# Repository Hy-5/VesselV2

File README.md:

# VesselV2
 Keyboard PCB build#2

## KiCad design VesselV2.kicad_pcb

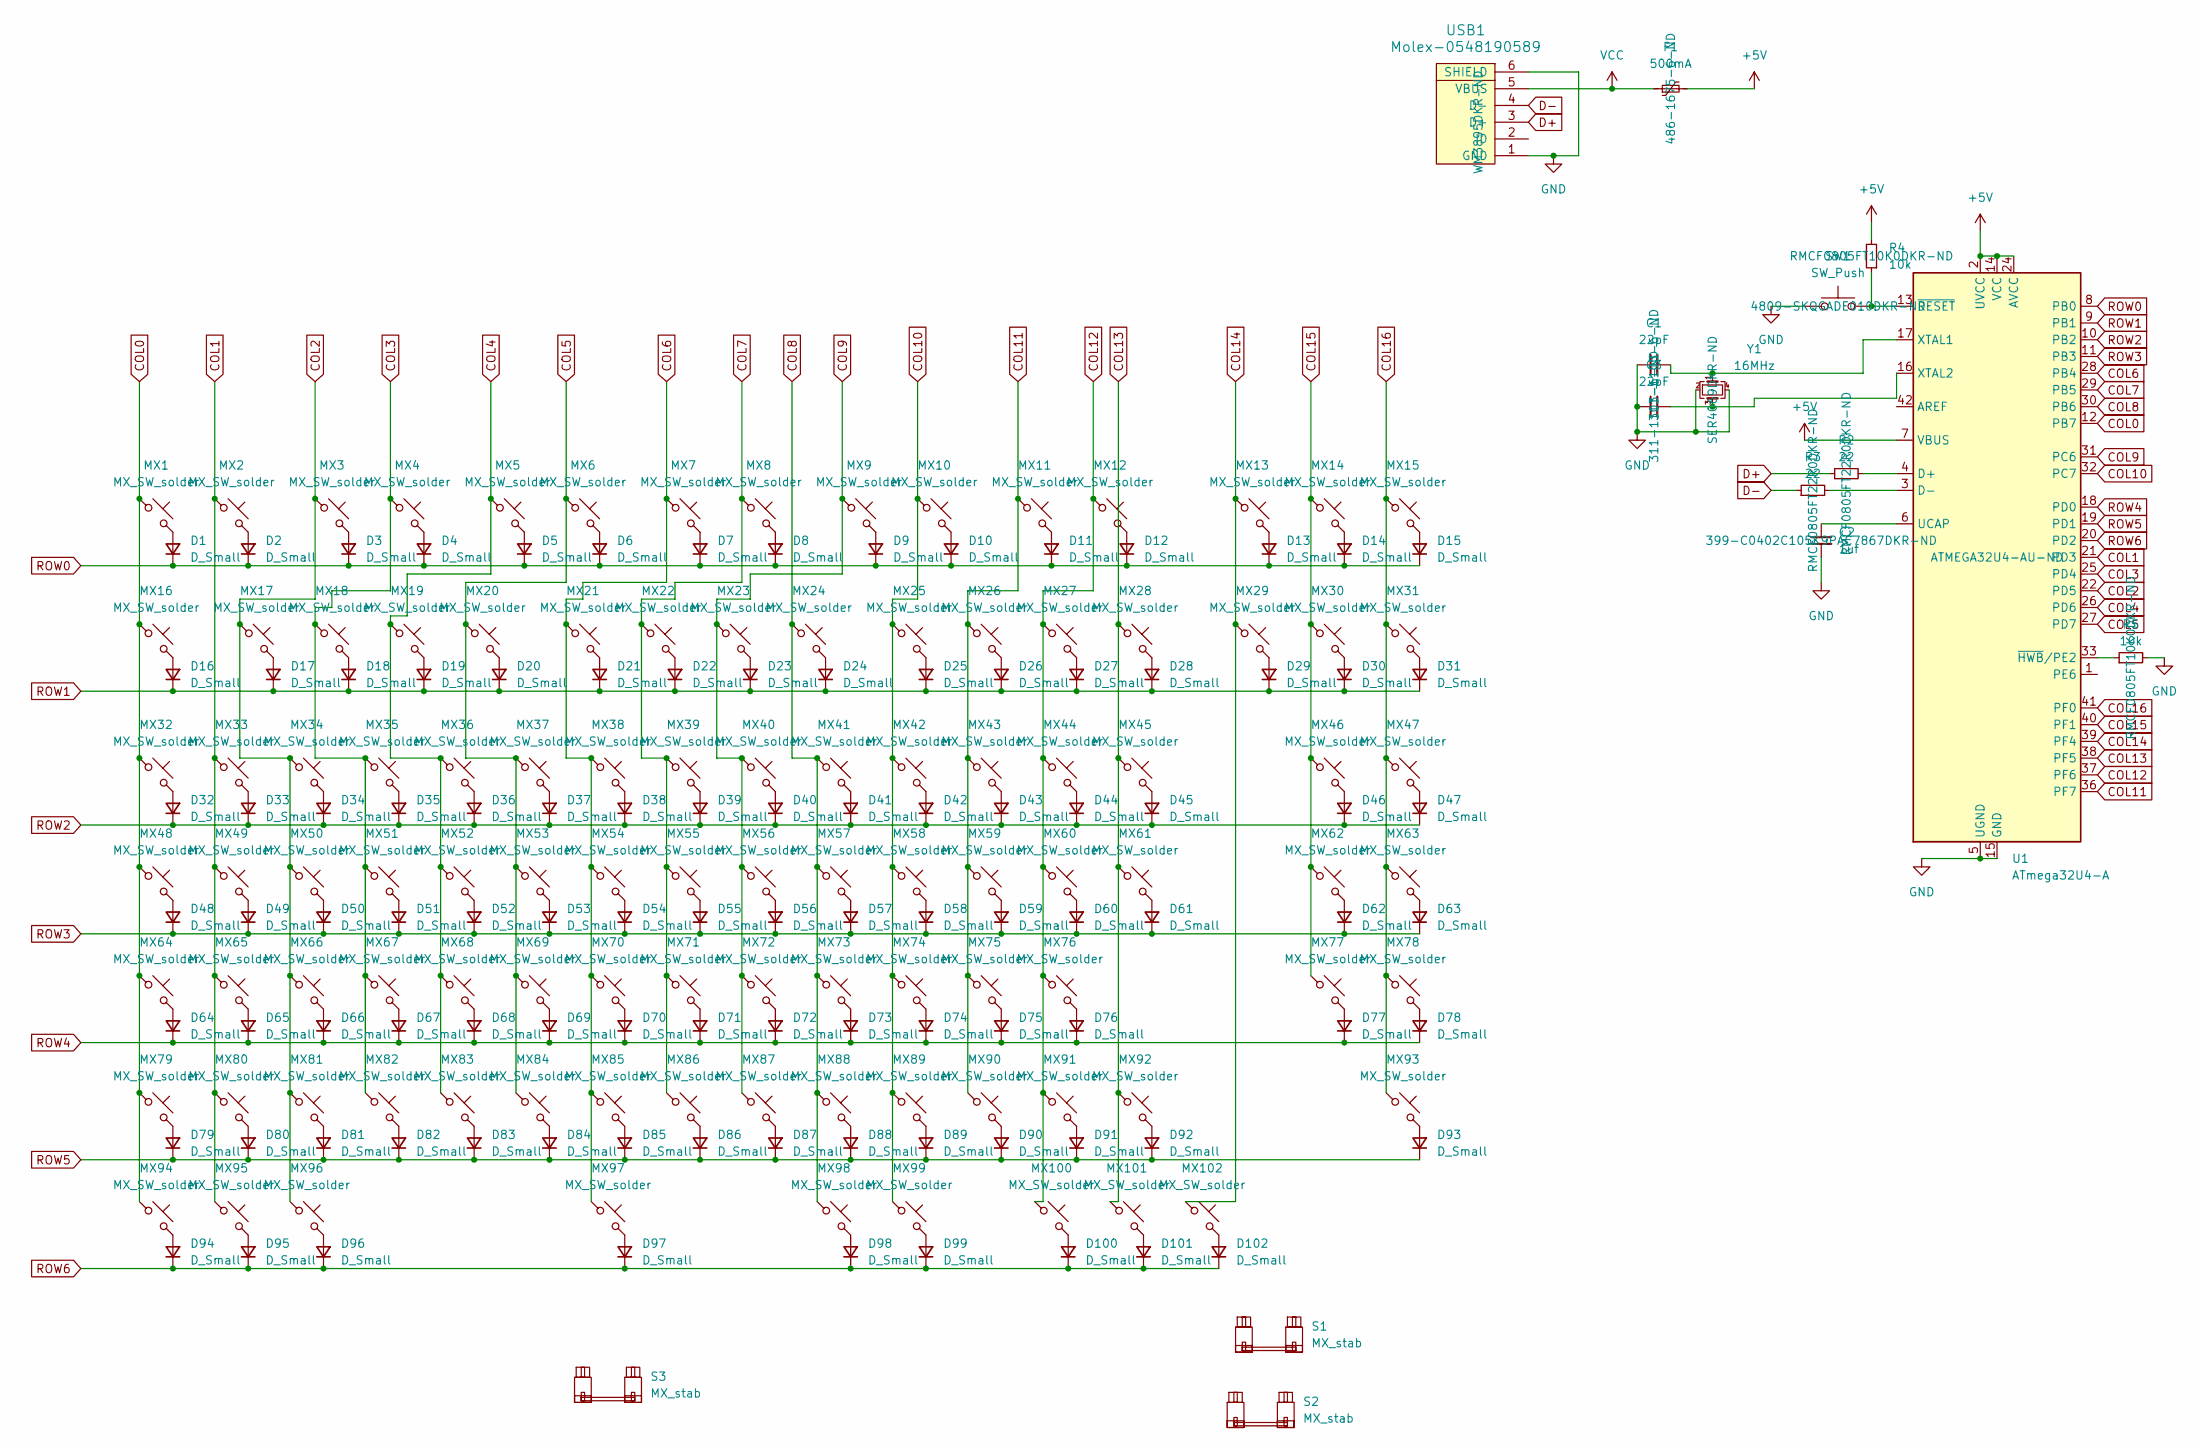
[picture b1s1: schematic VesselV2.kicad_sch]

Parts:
C1, C3: 22pF; C_0805_2012Metric_Pad1.18x1.45mm_HandSolder; MouserPartNumber 603-CC805JRNPO9BN220; DigikeyPartNumber 311-1103-6-ND
C2: 1uf; C_0805_2012Metric_Pad1.18x1.45mm_HandSolder; MouserPartNumber 80-C0402C105K9P; DigikeyPartNumber 399-C0402C105K9PAC7867DKR-ND
D1, D2, D3, D4, D5, D6, D7, D8, D9, D10, D11, D12, D13, D14, D15, D16, D17, D18, D19, D20, D21, D22, D23, D24, D25, D26, D27, D28, D29, D30, D31, D32, D33, D34, D35, D36, D37, D38, D39, D40, D41, D42, D43, D44, D45, D46, D47, D48, D49, D50, D51, D52, D53, D54, D55, D56, D57, D58, D59, D60, D61, D62, D63, D64, D65, D66, D67, D68, D69, D70, D71, D72, D73, D74, D75, D76, D77, D78, D79, D80, D81, D82, D83, D84, D85, D86, D87, D88, D89, D90, D91, D92, D93, D94, D95, D96, D97, D98, D99, D100, D101, D102: D_Small; D_SOD-123; ManufacturerPartNumber 1N4148W; DigikeyPartNumber 1N4148WTPMSDKR-ND
F1: 500mA; Fuse_1206_3216Metric_Pad1.42x1.75mm_HandSolder; MouserPartNumber 693-3413.0113.22; DigikeyPartNumber 486-1675-6-ND
MX1, MX2, MX3, MX4, MX5, MX6, MX7, MX8, MX9, MX10, MX11, MX12, MX13, MX14, MX15, MX16, MX17, MX18, MX19, MX20, MX21, MX22, MX23, MX24, MX25, MX26, MX27, MX28, MX29, MX30, MX31, MX32, MX33, MX34, MX35, MX36, MX37, MX38, MX39, MX40, MX41, MX42, MX43, MX44, MX46, MX47, MX49, MX50, MX51, MX52, MX53, MX54, MX55, MX56, MX57, MX58, MX59, MX60, MX62, MX63, MX65, MX66, MX67, MX68, MX69, MX70, MX71, MX72, MX73, MX74, MX75, MX76, MX77, MX78, MX80, MX81, MX82, MX83, MX84, MX85, MX86, MX87, MX88, MX89, MX90, MX92, MX93, MX100, MX101, MX102: MX_SW_solder; SW_Cherry_MX_PCB_1.00u
MX45: MX_SW_solder; SW_Cherry_MX_PCB_2.00u
MX48: MX_SW_solder; SW_Cherry_MX_PCB_1.50u
MX61: MX_SW_solder; SW_Cherry_MX_PCB_ISOEnter
MX64, MX91: MX_SW_solder; SW_Cherry_MX_PCB_1.75u
MX79, MX94, MX95, MX96, MX98, MX99: MX_SW_solder; SW_Cherry_MX_PCB_1.25u
MX97: MX_SW_solder; SW_Cherry_MX_PCB_6.25u
R2, R3: 22; R_0805_2012Metric_Pad1.20x1.40mm_HandSolder; MouserPartNumber 708-RMCF0805FT22R0; DigikeyPartNumber RMCF0805FT22R0DKR-ND
R4, R5: 10k; R_0805_2012Metric_Pad1.20x1.40mm_HandSolder; MouserPartNumber 708-RMCF0805FT10K0; DigikeyPartNumber RMCF0805FT10K0DKR-ND
S1, S2: MX_stab; Stabilizer_Cherry_MX_2.00u
S3: MX_stab; Stabilizer_Cherry_MX_6.25u
SW1: SW_Push; SKQG-1155865; ManufacturerPartNumber SKQGACE010; DigikeyPartNumber 4809-SKQGADE010DKR-ND
U1: ATmega32U4-A; TQFP-44_10x10mm_P0.8mm; MouserPartNumber 556-ATMEGA32U4-AU; DigikeyPartNumber ATMEGA32U4-AU-ND
USB1: Molex-0548190589; ManufacturerPartNumber 548190589; DigikeyPartNumber WM3895DKR-ND
Y1: 16MHz; Crystal_SMD_3225-4Pin_3.2x2.5mm_HandSoldering; MouserPartNumber 732-322516MF09Z-AC0; DigikeyPartNumber SER4069DKR-ND

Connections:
+5V: F1.2, R4.2, U1.2 (UVCC), U1.7 (VBUS), U1.14 (VCC), U1.24 (AVCC), U1.34 (VCC), U1.44 (AVCC)
COL0: MX1.1, MX16.1, MX32.1, MX48.1, MX64.1, MX79.1, MX94.1, U1.12 (PB7)
COL1: MX2.1, MX33.1, MX49.1, MX65.1, MX80.1, MX95.1, U1.21 (PD3)
COL2: MX3.1, MX17.1, MX34.1, MX50.1, MX66.1, MX81.1, MX96.1, U1.22 (PD5)
COL3: MX4.1, MX18.1, MX35.1, MX51.1, MX67.1, MX82.1, U1.25 (PD4)
COL4: MX5.1, MX19.1, MX36.1, MX52.1, MX68.1, MX83.1, U1.26 (PD6)
COL5: MX6.1, MX20.1, MX37.1, MX53.1, MX69.1, MX84.1, U1.27 (PD7)
COL6: MX7.1, MX21.1, MX38.1, MX54.1, MX70.1, MX85.1, MX97.1, U1.28 (PB4)
COL7: MX8.1, MX22.1, MX39.1, MX55.1, MX71.1, MX86.1, U1.29 (PB5)
COL8: MX24.1, MX41.1, MX57.1, MX73.1, MX88.1, MX98.1, U1.30 (PB6)
COL9: MX9.1, MX23.1, MX40.1, MX56.1, MX72.1, MX87.1, U1.31 (PC6)
COL10: MX10.1, MX25.1, MX42.1, MX58.1, MX74.1, MX89.1, MX99.1, U1.32 (PC7)
COL11: MX11.1, MX26.1, MX43.1, MX59.1, MX75.1, MX90.1, U1.36 (PF7)
COL12: MX12.1, MX27.1, MX44.1, MX60.1, MX76.1, MX91.1, MX100.1, U1.37 (PF6)
COL13: MX28.1, MX45.1, MX61.1, MX92.1, MX101.1, U1.38 (PF5)
COL14: MX13.1, MX29.1, MX102.1, U1.39 (PF4)
COL15: MX14.1, MX30.1, MX46.1, MX62.1, MX77.1, U1.40 (PF1)
COL16: MX15.1, MX31.1, MX47.1, MX63.1, MX78.1, MX93.1, U1.41 (PF0)
D+: R2.1, USB1.3 (D+)
D-: R3.1, USB1.4 (D-)
GND: C1.1, C2.2, C3.1, R5.2, SW1.1, U1.5 (UGND), U1.15 (GND), U1.23 (GND), U1.35 (GND), U1.43 (GND), USB1.1 (GND), USB1.6 (SHIELD), Y1.2, Y1.4
unnamed: D1.2 (A), MX1.2
unnamed: D2.2 (A), MX2.2
unnamed: D3.2 (A), MX3.2
unnamed: D4.2 (A), MX4.2
unnamed: D5.2 (A), MX5.2
unnamed: D6.2 (A), MX6.2
unnamed: D7.2 (A), MX7.2
unnamed: D8.2 (A), MX8.2
unnamed: D9.2 (A), MX9.2
unnamed: D10.2 (A), MX10.2
unnamed: D11.2 (A), MX11.2
unnamed: D12.2 (A), MX12.2
unnamed: D13.2 (A), MX13.2
unnamed: D14.2 (A), MX14.2
unnamed: D15.2 (A), MX15.2
unnamed: D16.2 (A), MX16.2
unnamed: D17.2 (A), MX17.2
unnamed: D18.2 (A), MX18.2
unnamed: D19.2 (A), MX19.2
unnamed: D20.2 (A), MX20.2
unnamed: D21.2 (A), MX21.2
unnamed: D22.2 (A), MX22.2
unnamed: D23.2 (A), MX23.2
unnamed: D24.2 (A), MX24.2
unnamed: D25.2 (A), MX25.2
unnamed: D26.2 (A), MX26.2
unnamed: D27.2 (A), MX27.2
unnamed: D28.2 (A), MX28.2
unnamed: D29.2 (A), MX29.2
unnamed: D30.2 (A), MX30.2
unnamed: D31.2 (A), MX31.2
unnamed: D32.2 (A), MX32.2
unnamed: D33.2 (A), MX33.2
unnamed: D34.2 (A), MX34.2
unnamed: D35.2 (A), MX35.2
unnamed: D36.2 (A), MX36.2
unnamed: D37.2 (A), MX37.2
unnamed: D38.2 (A), MX38.2
unnamed: D39.2 (A), MX39.2
unnamed: D40.2 (A), MX40.2
unnamed: D41.2 (A), MX41.2
unnamed: D42.2 (A), MX42.2
unnamed: D43.2 (A), MX43.2
unnamed: D44.2 (A), MX44.2
unnamed: D45.2 (A), MX45.2
unnamed: D46.2 (A), MX46.2
unnamed: D47.2 (A), MX47.2
unnamed: D48.2 (A), MX48.2
unnamed: D49.2 (A), MX49.2
unnamed: D50.2 (A), MX50.2
unnamed: D51.2 (A), MX51.2
unnamed: D52.2 (A), MX52.2
unnamed: D53.2 (A), MX53.2
unnamed: D54.2 (A), MX54.2
unnamed: D55.2 (A), MX55.2
unnamed: D56.2 (A), MX56.2
unnamed: D57.2 (A), MX57.2
unnamed: D58.2 (A), MX58.2
unnamed: D59.2 (A), MX59.2
unnamed: D60.2 (A), MX60.2
unnamed: D61.2 (A), MX61.2
unnamed: D62.2 (A), MX62.2
unnamed: D63.2 (A), MX63.2
unnamed: D64.2 (A), MX64.2
unnamed: D65.2 (A), MX65.2
unnamed: D66.2 (A), MX66.2
unnamed: D67.2 (A), MX67.2
unnamed: D68.2 (A), MX68.2
unnamed: D69.2 (A), MX69.2
unnamed: D70.2 (A), MX70.2
unnamed: D71.2 (A), MX71.2
unnamed: D72.2 (A), MX72.2
unnamed: D73.2 (A), MX73.2
unnamed: D74.2 (A), MX74.2
unnamed: D75.2 (A), MX75.2
unnamed: D76.2 (A), MX76.2
unnamed: D77.2 (A), MX77.2
unnamed: D78.2 (A), MX78.2
unnamed: D79.2 (A), MX79.2
unnamed: D80.2 (A), MX80.2
unnamed: D81.2 (A), MX81.2
unnamed: D82.2 (A), MX82.2
unnamed: D83.2 (A), MX83.2
unnamed: D84.2 (A), MX84.2
unnamed: D85.2 (A), MX85.2
unnamed: D86.2 (A), MX86.2
unnamed: D87.2 (A), MX87.2
unnamed: D88.2 (A), MX88.2
unnamed: D89.2 (A), MX89.2
unnamed: D90.2 (A), MX90.2
unnamed: D91.2 (A), MX91.2
unnamed: D92.2 (A), MX92.2
unnamed: D93.2 (A), MX93.2
unnamed: D94.2 (A), MX94.2
unnamed: D95.2 (A), MX95.2
unnamed: D96.2 (A), MX96.2
unnamed: D97.2 (A), MX97.2
unnamed: D98.2 (A), MX98.2
unnamed: D99.2 (A), MX99.2
unnamed: D100.2 (A), MX100.2
unnamed: D101.2 (A), MX101.2
unnamed: D102.2 (A), MX102.2
unnamed: R2.2, U1.4 (D+)
unnamed: R3.2, U1.3 (D-)
unnamed: C2.1, U1.6 (UCAP)
unnamed: C1.2, U1.17 (XTAL1), Y1.1
unnamed: C3.2, U1.16 (XTAL2), Y1.3
unnamed: R5.1, U1.33 (~HWB/PE2)
unnamed: R4.1, SW1.2, U1.13 (~RESET)
ROW0: D1.1 (K), D2.1 (K), D3.1 (K), D4.1 (K), D5.1 (K), D6.1 (K), D7.1 (K), D8.1 (K), D9.1 (K), D10.1 (K), D11.1 (K), D12.1 (K), D13.1 (K), D14.1 (K), D15.1 (K), U1.8 (PB0)
ROW1: D16.1 (K), D17.1 (K), D18.1 (K), D19.1 (K), D20.1 (K), D21.1 (K), D22.1 (K), D23.1 (K), D24.1 (K), D25.1 (K), D26.1 (K), D27.1 (K), D28.1 (K), D29.1 (K), D30.1 (K), D31.1 (K), U1.9 (PB1)
ROW2: D32.1 (K), D33.1 (K), D34.1 (K), D35.1 (K), D36.1 (K), D37.1 (K), D38.1 (K), D39.1 (K), D40.1 (K), D41.1 (K), D42.1 (K), D43.1 (K), D44.1 (K), D45.1 (K), D46.1 (K), D47.1 (K), U1.10 (PB2)
ROW3: D48.1 (K), D49.1 (K), D50.1 (K), D51.1 (K), D52.1 (K), D53.1 (K), D54.1 (K), D55.1 (K), D56.1 (K), D57.1 (K), D58.1 (K), D59.1 (K), D60.1 (K), D61.1 (K), D62.1 (K), D63.1 (K), U1.11 (PB3)
ROW4: D64.1 (K), D65.1 (K), D66.1 (K), D67.1 (K), D68.1 (K), D69.1 (K), D70.1 (K), D71.1 (K), D72.1 (K), D73.1 (K), D74.1 (K), D75.1 (K), D76.1 (K), D77.1 (K), D78.1 (K), U1.18 (PD0)
ROW5: D79.1 (K), D80.1 (K), D81.1 (K), D82.1 (K), D83.1 (K), D84.1 (K), D85.1 (K), D86.1 (K), D87.1 (K), D88.1 (K), D89.1 (K), D90.1 (K), D91.1 (K), D92.1 (K), D93.1 (K), U1.19 (PD1)
ROW6: D94.1 (K), D95.1 (K), D96.1 (K), D97.1 (K), D98.1 (K), D99.1 (K), D100.1 (K), D101.1 (K), D102.1 (K), U1.20 (PD2)
VCC: F1.1, USB1.5 (VBUS)

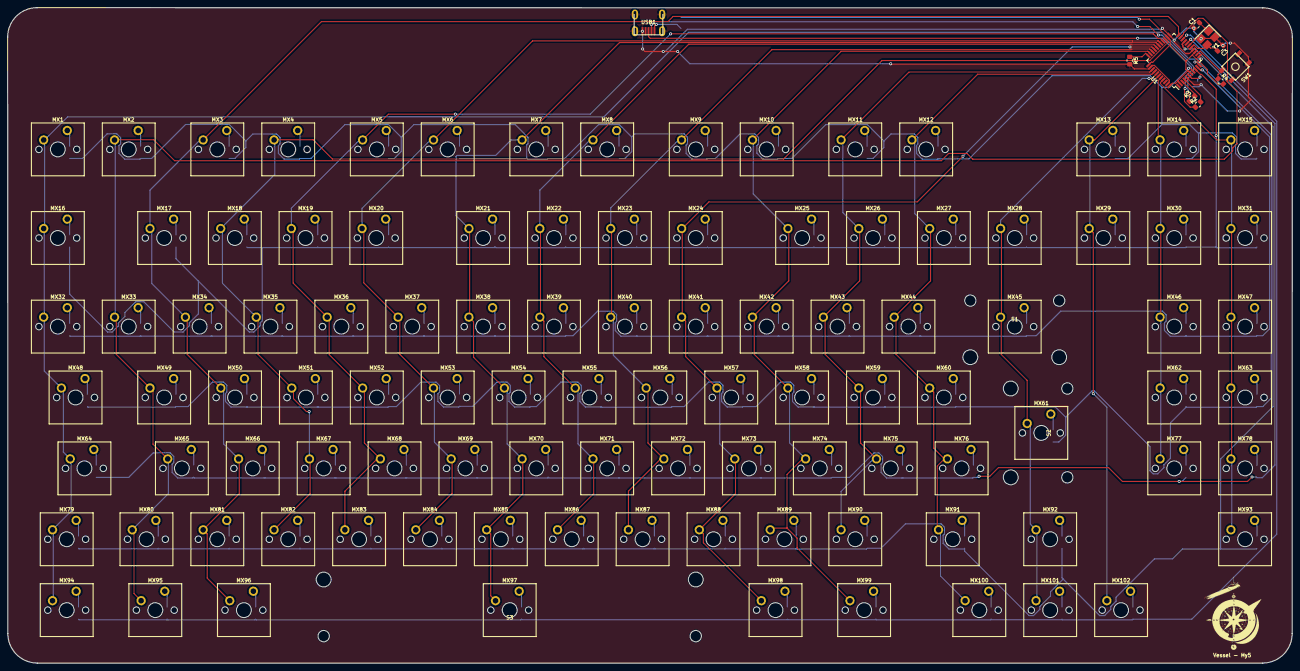
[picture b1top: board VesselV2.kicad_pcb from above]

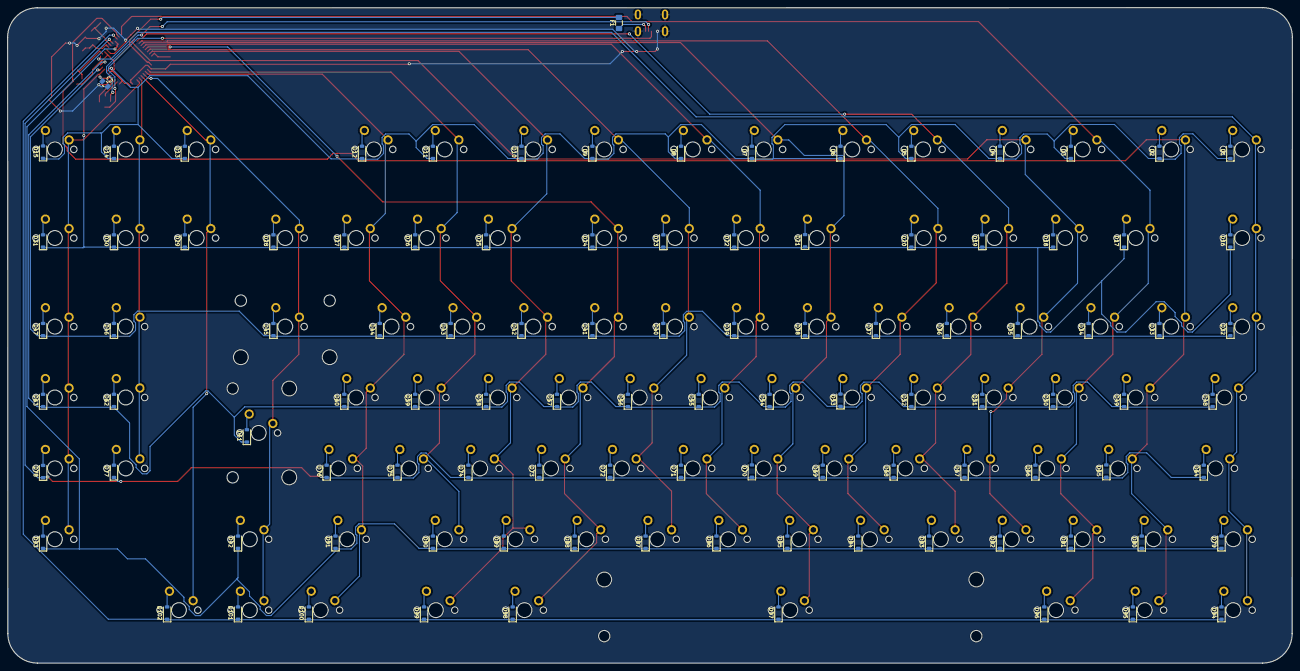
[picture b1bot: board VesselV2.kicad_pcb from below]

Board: 2 copper layers, 345.3 x 176.2 mm, 220 parts (104 on the bottom side), 138 nets.

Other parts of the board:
?: ?; VesselLogoPCB

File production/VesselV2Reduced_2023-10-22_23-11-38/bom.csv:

Designator,Footprint,Quantity,Value,LCSC Part #
"C1, C3",0805,2,22pF,
C2,0805,1,1uf,
C5,0805,1,22uF,
"D1, D10, D100, D101, D102, D11, D12, D13, D14, D15, D16, D17, D18, D19, D2, D20, D21, D22, D23, D24, D25, D26, D27, D28, D29, D3, D30, D31, D32, D33, D34, D35, D36, D37, D38, D39, D4, D40, D41, D42, D43, D44, D45, D46, D47, D48, D49, D5, D50, D51, D52, D53, D54, D55, D56, D57, D58, D59, D6, D60, D61, D62, D63, D64, D65, D66, D67, D68, D69, D7, D70, D71, D72, D73, D74, D75, D76, D77, D78, D79, D8, D80, D81, D82, D83, D84, D85, D86, D87, D88, D89, D9, D90, D91, D92, D93, D94, D95, D96, D97, D98, D99",D_SOD-123,102,D_Small,
D103,LED_Inolux_IN-PI554FCH_PLCC4_5.0x5.0mm_P3.2mm,1,Inolux_IN-PI554FCH,
F2,1206,1,500mA,
J1,USB_Mini-B_Lumberg_2486_01_Horizontal,1,USB_B_Mini,
"MX1, MX10, MX100, MX101, MX102, MX11, MX12, MX13, MX14, MX15, MX16, MX17, MX18, MX19, MX2, MX20, MX21, MX22, MX23, MX24, MX25, MX26, MX27, MX28, MX29, MX3, MX30, MX31, MX32, MX33, MX34, MX35, MX36, MX37, MX38, MX39, MX4, MX40, MX41, MX42, MX43, MX44, MX46, MX47, MX49, MX5, MX50, MX51, MX52, MX53, MX54, MX55, MX56, MX57, MX58, MX59, MX6, MX60, MX62, MX63, MX65, MX66, MX67, MX68, MX69, MX7, MX70, MX71, MX72, MX73, MX74, MX75, MX76, MX77, MX78, MX8, MX80, MX81, MX82, MX83, MX84, MX85, MX86, MX87, MX88, MX89, MX9, MX90, MX92, MX93",SW_Cherry_MX_PCB_1.00u,90,MX_SW_solder,
MX45,SW_Cherry_MX_PCB_2.00u,1,MX_SW_solder,
MX48,SW_Cherry_MX_PCB_1.50u,1,MX_SW_solder,
MX61,SW_Cherry_MX_PCB_ISOEnter,1,MX_SW_solder,
"MX64, MX91",SW_Cherry_MX_PCB_1.75u,2,MX_SW_solder,
"MX79, MX94, MX95, MX96, MX98, MX99",SW_Cherry_MX_PCB_1.25u,6,MX_SW_solder,
MX97,SW_Cherry_MX_PCB_6.25u,1,MX_SW_solder,
"R2, R3",0805,2,22,
"R4, R5",0805,2,10k,
R6,0805,1,350,
"S1, S2",Stabilizer_Cherry_MX_2.00u,2,MX_stab,
S3,Stabilizer_Cherry_MX_6.25u,1,MX_stab,
SW1,SKQG-1155865,1,SW_Push,
U1,TQFP-44_10x10mm_P0.8mm,1,ATmega32U4-A,
Y1,Crystal_SMD_3225-4Pin_3.2x2.5mm_HandSoldering,1,16MHz,

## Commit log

2023-10-19 Initial Commit - Schematics and Footprints assigned
2023-10-19 Late night PCB organization (WIP)
2023-10-19 Pcb build done - Adding crystal & labels
2023-10-19 Footprint Assignment
2023-10-19 Reset switch & USB Submodules added
2023-10-19 Footprint Assignment & Part Number association
2023-10-19 Edge cuts done - Datasheet info filled in - Preliminary Bom generated
2023-10-20 Mouser partNumber fields Update - BOM Update
2023-10-20 Preliminary routing, Zone fill & DRC
2023-10-20 Working PCB - Routing and DRC WIP
2023-10-21 Fixed routing errors - except USB footprint shape
2023-10-21 Switch footprint swap - 3d models fixed - Routing (re)done - No errors other than USB footprint
2023-10-22 Led Logo symbol and added - useless files deleted
2023-10-22 USB connector swap and rerouting - No more errors
2023-10-23 Added reduced size pcb
2023-10-27 Grid origin set- Prep for Freecad case design
2023-10-29 Added M3 mounting holes
